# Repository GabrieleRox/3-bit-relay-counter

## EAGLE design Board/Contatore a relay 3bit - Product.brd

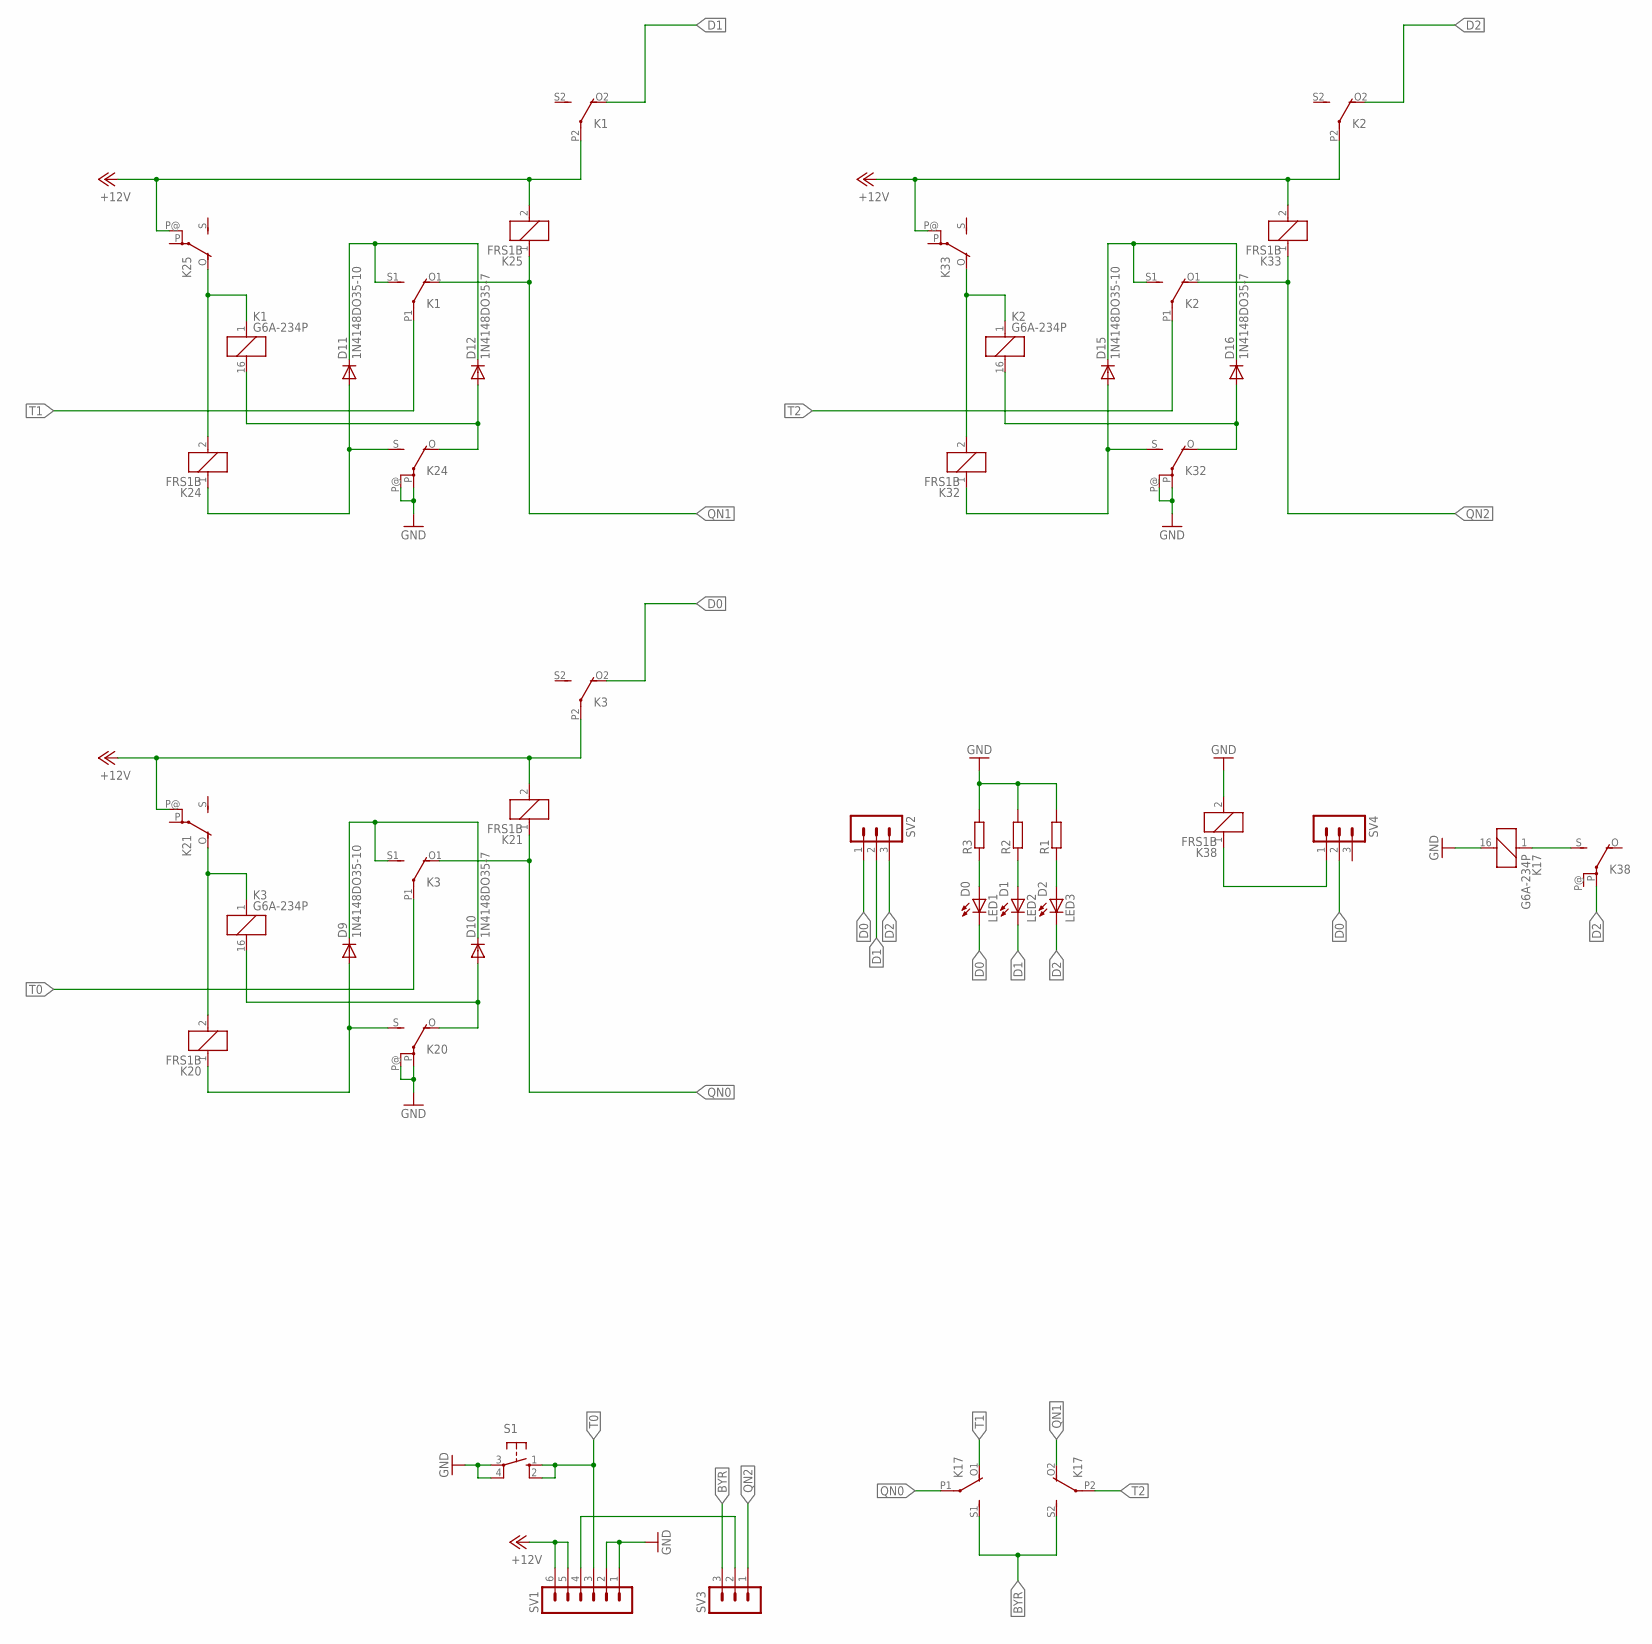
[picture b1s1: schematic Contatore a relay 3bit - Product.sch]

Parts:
D9, D11, D15: 1N4148DO35-10; DO35-10
D10, D12, D16: 1N4148DO35-7; DO35-7
K1, K2, K3, K17: G6A-234P
K20, K21, K24, K25, K32, K33, K38: FRS1B
LED1: D0; LED3MM
LED2: D1; LED3MM
LED3: D2; LED3MM
R1, R2, R3: R-EU_M0805; M0805
S1: 10-XX; B3F-10XX
SV1: MA06-1
SV2, SV3, SV4: MA03-1

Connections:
+12V: K1.P2, K2.P2, K3.P2, K21.2, K21.P@, K25.2, K25.P@, K33.2, K33.P@, SV1.5, SV1.6
BYR: K17.S1 (S), K17.S2 (S), SV3.3
D0: K3.O2 (O), LED1.K (C), SV2.1, SV4.2
D1: K1.O2 (O), LED2.K (C), SV2.2
D2: K2.O2 (O), K38.P, LED3.K (C), SV2.3
GND: K17.16 (2), K20.P, K20.P@, K24.P, K24.P@, K32.P, K32.P@, K38.2, R1.2, R2.2, R3.2, S1.3, S1.4 (P1), SV1.1, SV1.2
unnamed: SV1.4, SV3.2
unnamed: K38.1, SV4.1
unnamed: D10.A, K3.16 (2), K20.O
unnamed: D9.A, K20.1, K20.S
unnamed: K3.1, K20.2, K21.O
unnamed: D9.C, D10.C, K3.S1 (S)
unnamed: D12.A, K1.16 (2), K24.O
unnamed: D11.A, K24.1, K24.S
unnamed: K1.1, K24.2, K25.O
unnamed: D11.C, D12.C, K1.S1 (S)
unnamed: D16.A, K2.16 (2), K32.O
unnamed: D15.A, K32.1, K32.S
unnamed: K2.1, K32.2, K33.O
unnamed: D15.C, D16.C, K2.S1 (S)
unnamed: K17.1, K38.S
unnamed: LED1.A, R3.1
unnamed: LED2.A, R2.1
unnamed: LED3.A, R1.1
QN0: K3.O1 (O), K17.P1, K21.1
QN1: K1.O1 (O), K17.O2 (O), K25.1
QN2: K2.O1 (O), K33.1, SV3.1
T0: K3.P1, S1.1 (S), S1.2 (S1), SV1.3
T1: K1.P1, K17.O1 (O)
T2: K2.P1, K17.P2

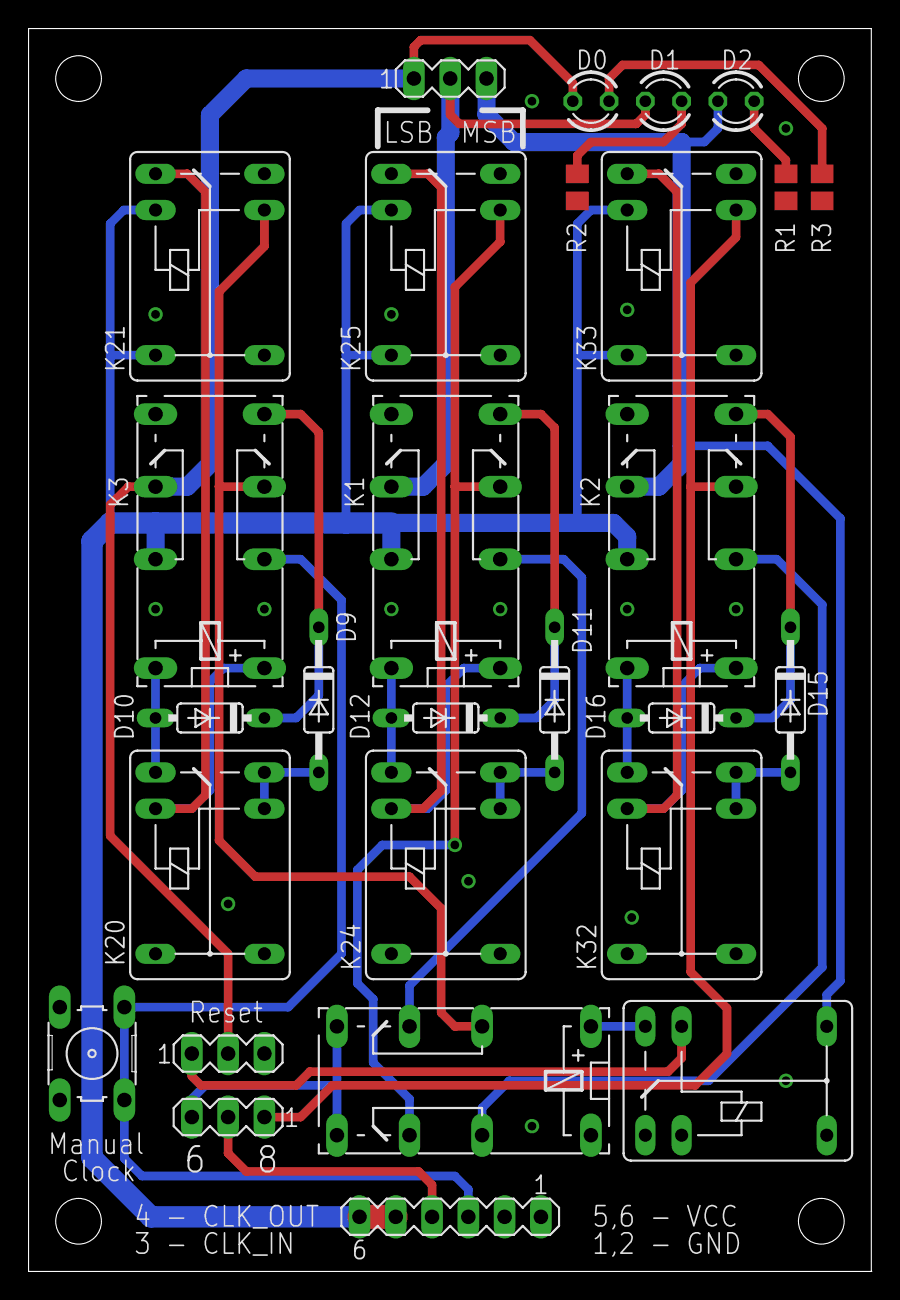
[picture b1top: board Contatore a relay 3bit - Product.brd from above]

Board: 2 copper layers, 59.0 x 87.0 mm, 28 parts (0 on the bottom side), 30 nets.

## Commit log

2022-02-11 First Upload
